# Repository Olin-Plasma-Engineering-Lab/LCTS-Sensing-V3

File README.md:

# LCTS-Sensing-V3

This is the repository for the sensing system used by the Olin Plasma Engineering Lab (OPEL) to measure thrust on the Low-Cost Thrust Stand.

## Brief System Overview
The system is comprised of two boards: a sender and a receiver. The sender is located in the vacuum chamber and is connected to a force sensor that measures thrust produced by the thrusters. The receiver board is located outside the vacuum chamber and exists to receive data sent by the sender board. The boards are connected via a wiring harness and electrical feedthrough on the vacuum chamber, and communicate using I2C.

The system allows for two way communication. This gets used so that the calibration system on the thrust stand within the vacuum chamber can be controlled using the receiver board outside the chamber.

## Repository Organization

- `code/`: This contains the code used by the systems
    - `Microcontroller/`: Code that gets uploaded to the microcontrollers
        - `Arduino/`: Arduino code that gets uploaded to the microcontrollers
            - `receiver/`: code for the receiver board
            - `sender/` (depreicated): code for the sender board for use with **STEPPER MOTOR CALIBRATION**
            - `sender_servo_calibration/`: code for the sender board for use with **SERVO MOTOR CALIBRATION** This is the most up to date script and the code that is actually used on the sender board
        - `Micropython/`: Location for future microcontroller code written in MicroPython. Not currently used but contains the MicroPython firmware
- `Testing/`: Contain a Python script that was used as a preliminary test for saving data to a CSV
- `data/`: Data recorded from unlabeled thruster tests
- `Hardware/`: KiCad projects and other needed files for the sender and receiver PCBs
    - `assets/`: OPEL logo for use on PCBs
    - `Parts/`: Parts needed fro the KiCad Project files
    - `receiver/`: KiCad project files for the receiver PCB
    - `sender/`: KiCad project files for the sender PCB
- `sensing_processor.py`: Script that is used to read data from the receiver and save to a CSV
    
##

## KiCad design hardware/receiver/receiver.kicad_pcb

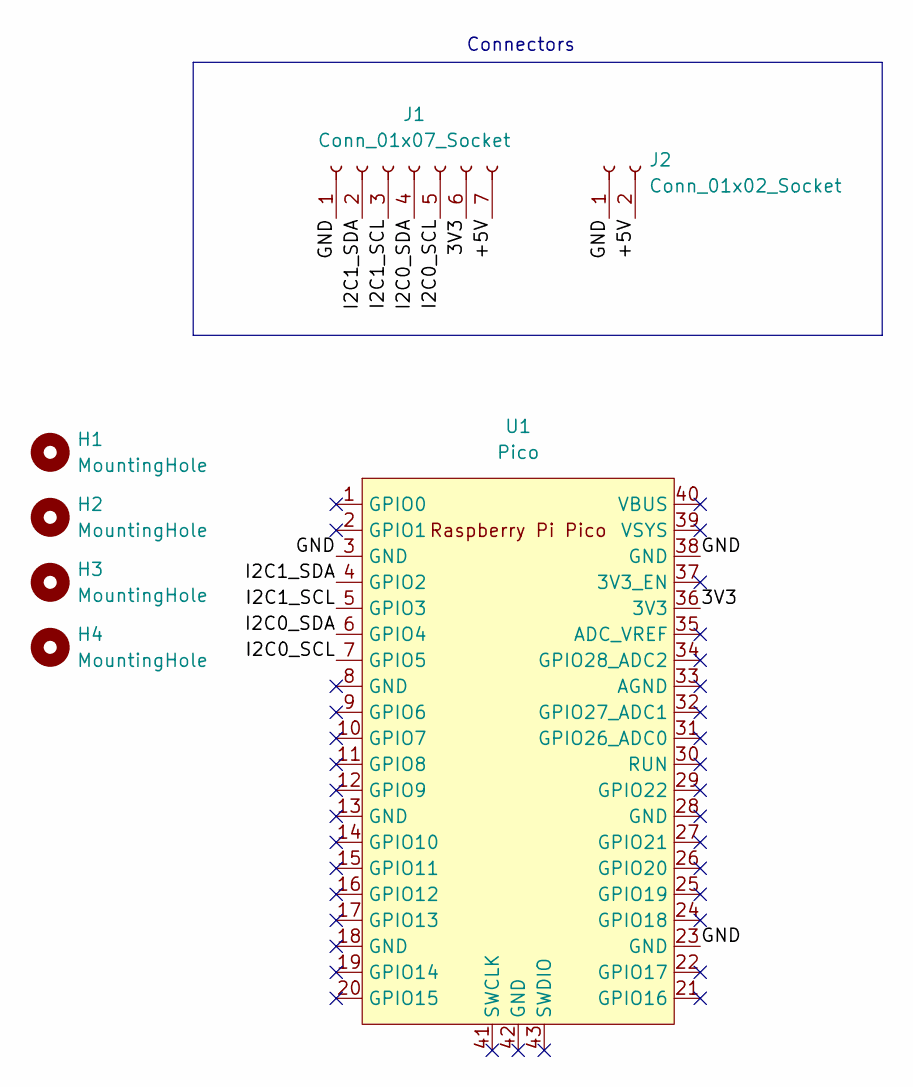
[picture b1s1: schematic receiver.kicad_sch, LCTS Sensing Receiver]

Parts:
H1, H2, H3, H4: MountingHole; MountingHole_2.2mm_M2
J1: Conn_01x07_Socket; JST_PH_B7B-PH-K_1x07_P2.00mm_Vertical
J2: Conn_01x02_Socket; JST_PH_B2B-PH-K_1x02_P2.00mm_Vertical
U1: Pico; RaspberryPi_Pico_Common_THT

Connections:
/3V3: J1.6, U1.36 (3V3)
/+5V: J1.7, J2.2
/GND: J1.1, J2.1, U1.3 (GND), U1.23 (GND), U1.38 (GND)
/I2C0_SCL: J1.5, U1.7 (GPIO5)
/I2C0_SDA: J1.4, U1.6 (GPIO4)
/I2C1_SCL: J1.3, U1.5 (GPIO3)
/I2C1_SDA: J1.2, U1.4 (GPIO2)

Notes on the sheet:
Connectors

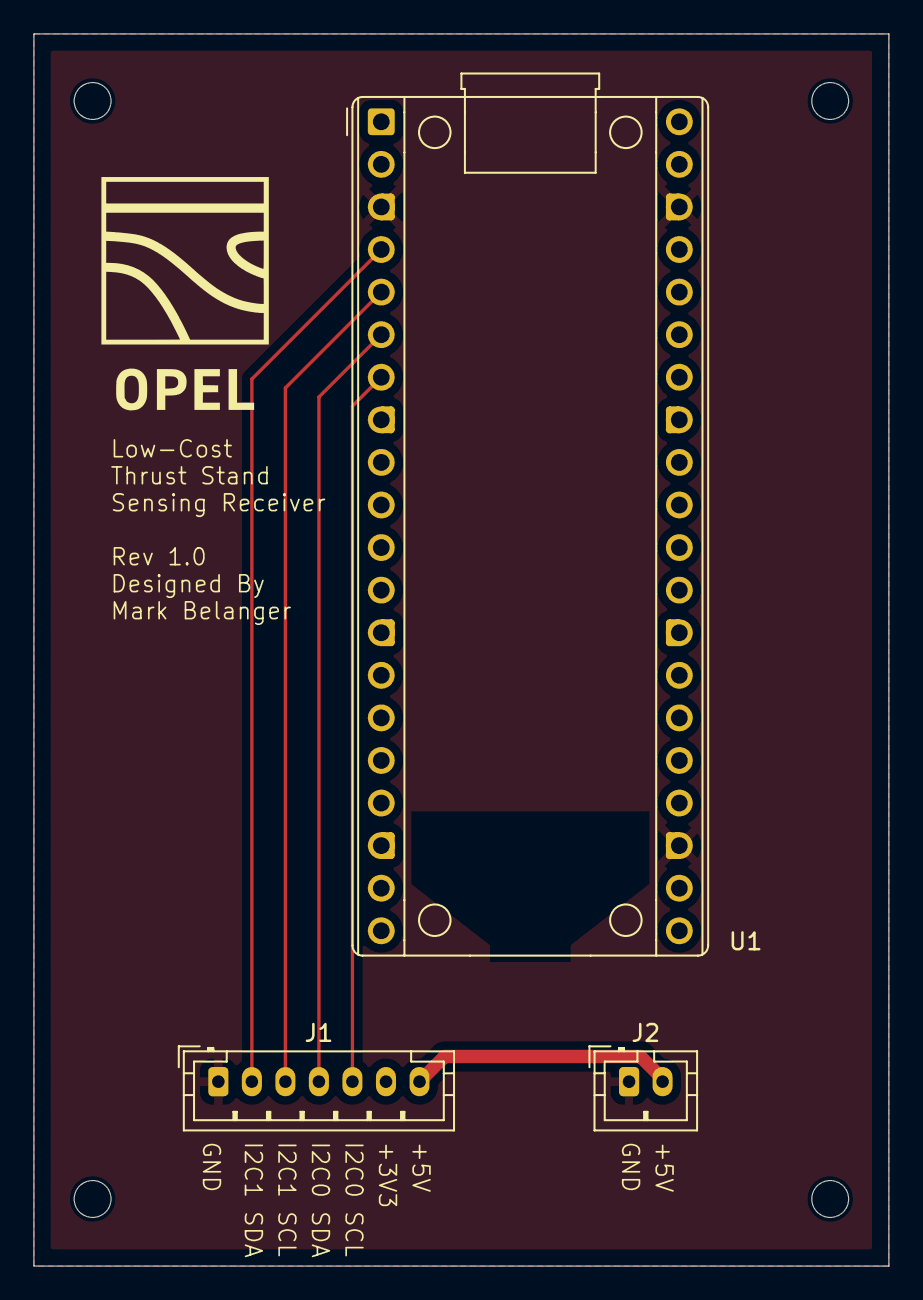
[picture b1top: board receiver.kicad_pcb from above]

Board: 2 copper layers, 51.0 x 73.5 mm, 7 parts (0 on the bottom side), 7 nets.

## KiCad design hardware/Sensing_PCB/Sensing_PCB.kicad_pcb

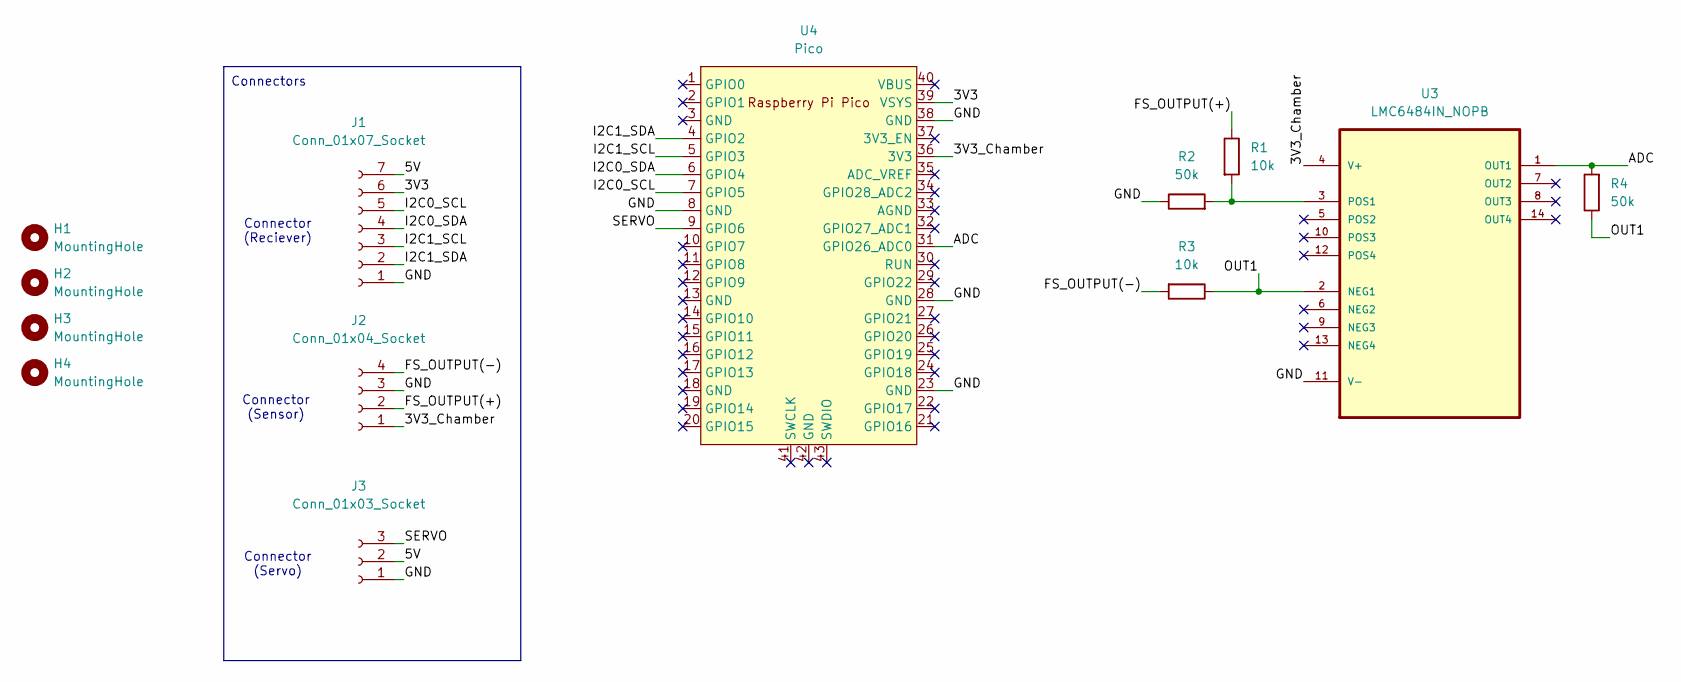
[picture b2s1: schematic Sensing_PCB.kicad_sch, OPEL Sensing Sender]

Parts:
H1, H2, H3, H4: MountingHole; MountingHole_2.2mm_M2
J1: Conn_01x07_Socket; JST_PH_B7B-PH-K_1x07_P2.00mm_Vertical
J2: Conn_01x04_Socket; JST_PH_B4B-PH-K_1x04_P2.00mm_Vertical
J3: Conn_01x03_Socket; JST_PH_B3B-PH-K_1x03_P2.00mm_Vertical
R1, R3: 10k; R_0603_1608Metric
R2, R4: 50k; R_0603_1608Metric
U3: LMC6484IN_NOPB; DIP254P762X508-14; MPN LMC6484IN/NOPB
U4: Pico; RPi_Pico_SMD_TH

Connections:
/3V3: J1.6, U4.39 (VSYS)
/3V3_Chamber: J2.1, U3.4 (V+), U4.36 (3V3)
/5V: J1.7, J3.2
/ADC: R4.2, U3.1 (OUT1), U4.31 (GPIO26_ADC0)
/FS_OUTPUT(+): J2.2, R1.1
/FS_OUTPUT(-): J2.4, R3.2
/GND: J1.1, J2.3, J3.1, R2.1, U3.11 (V-), U4.8 (GND), U4.23 (GND), U4.28 (GND), U4.38 (GND)
/I2C0_SCL: J1.5, U4.7 (GPIO5)
/I2C0_SDA: J1.4, U4.6 (GPIO4)
/I2C1_SCL: J1.3, U4.5 (GPIO3)
/I2C1_SDA: J1.2, U4.4 (GPIO2)
/OUT1: R3.1, R4.1, U3.2 (NEG1)
/SERVO: J3.3, U4.9 (GPIO6)
unnamed: R1.2, R2.2, U3.3 (POS1)

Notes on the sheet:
Connector (Servo)
Connector (Sensor)
Connectors
Connector (Reciever)

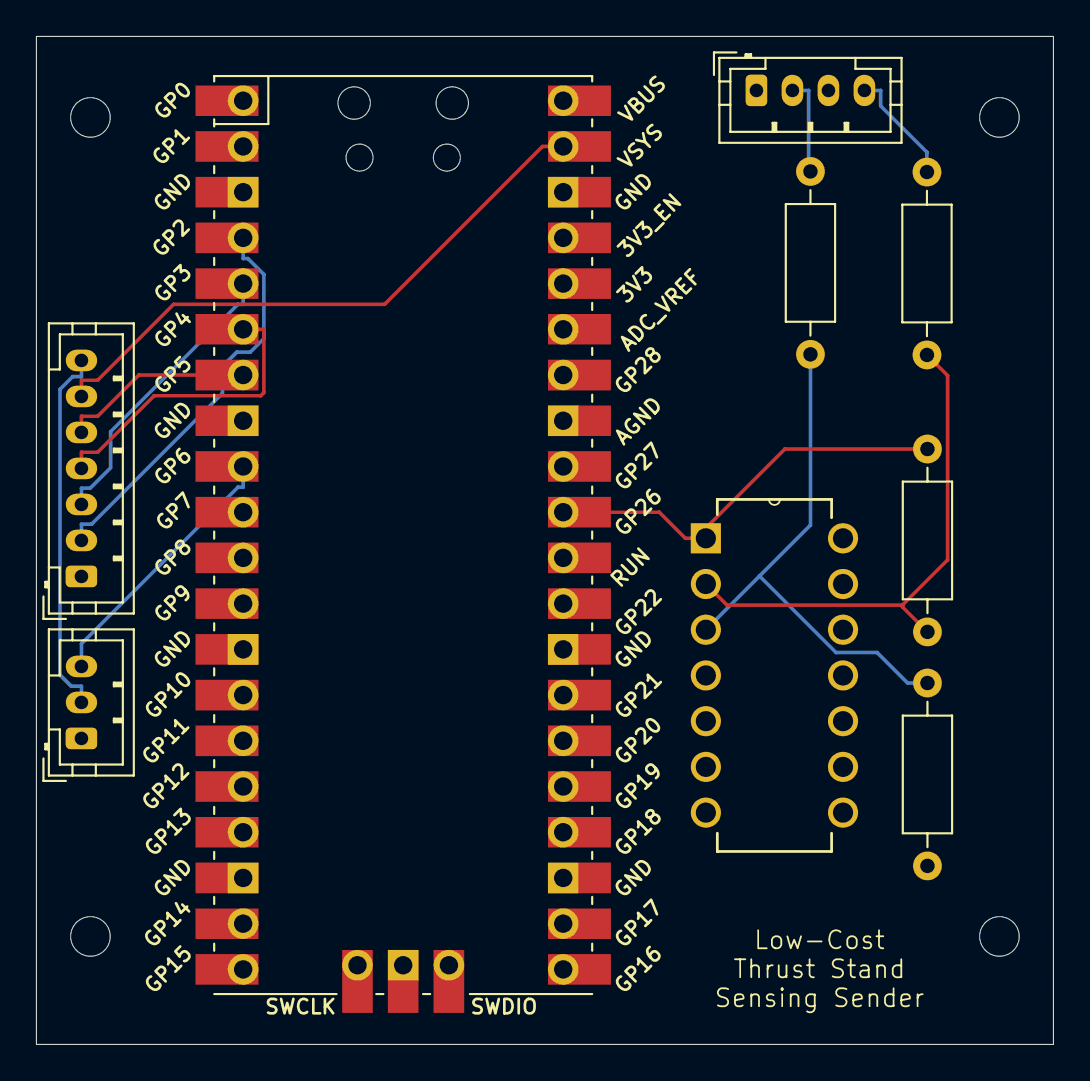
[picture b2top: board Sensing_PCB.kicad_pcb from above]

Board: 2 copper layers, 56.5 x 56.0 mm, 14 parts (1 on the bottom side), 14 nets.

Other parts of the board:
G1: LOGO; opel_logo

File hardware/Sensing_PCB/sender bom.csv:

Id,Designator,Footprint,Quantity,Designation,Supplier and ref
1,R2,R_0603_1608Metric,2,50k,,
2,U3,DIP254P762X508-14,1,LMC6484IN_NOPB,,
3,J1,JST_PH_B7B-PH-K_1x07_P2.00mm_Vertical,1,Conn_01x07_Socket,,
4,J3,JST_PH_B3B-PH-K_1x03_P2.00mm_Vertical,1,Conn_01x03_Socket,,
5,R1,R_0603_1608Metric,2,10k,,
6,U4,RPi_Pico_SMD_TH,1,Pico,,
7,J2,JST_PH_B4B-PH-K_1x04_P2.00mm_Vertical,1,Conn_01x04_Socket,,
8,R4,R_0603_1608Metric,2,50k,,
9,R3,R_0603_1608Metric,2,10k,,

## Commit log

2024-09-13 Add all content from V2 system
2024-09-13 Add MicroPython organization and firmware
2024-10-04 remove commented out code
2024-10-08 Add Sensing PCB KiCad Files
2024-10-09 Add KiCad project for receiver PCB
2024-10-09 Remove unused pico library
2024-10-10 Update receiver PCB
    Power and ground planes added
    Logo and title added to silkscreen
2024-10-10 Add OPEL logo png file
2024-10-10 Add Rev.1 of Sender PCB
2024-10-10 Add KiCad-RP-Pico Submodule
2024-10-11 Update receiver PCB and add gerber files
    Added mounting holes, changes silk screen, and organized the schematic
2024-10-11 Update Sender PCB
2024-10-21 New Sender Design
2024-10-22 Add gerber files to both boards
    BOM and footprint placement also added for sender board
2024-10-22 Rename Sensing_PCB to sender
2024-10-22 Update readme to include overview and organization
2024-11-12 Add photos of the system
2024-11-19 Add annotated pic for receiver wiring harness
2024-11-22 Add pictures of the various sensing components
